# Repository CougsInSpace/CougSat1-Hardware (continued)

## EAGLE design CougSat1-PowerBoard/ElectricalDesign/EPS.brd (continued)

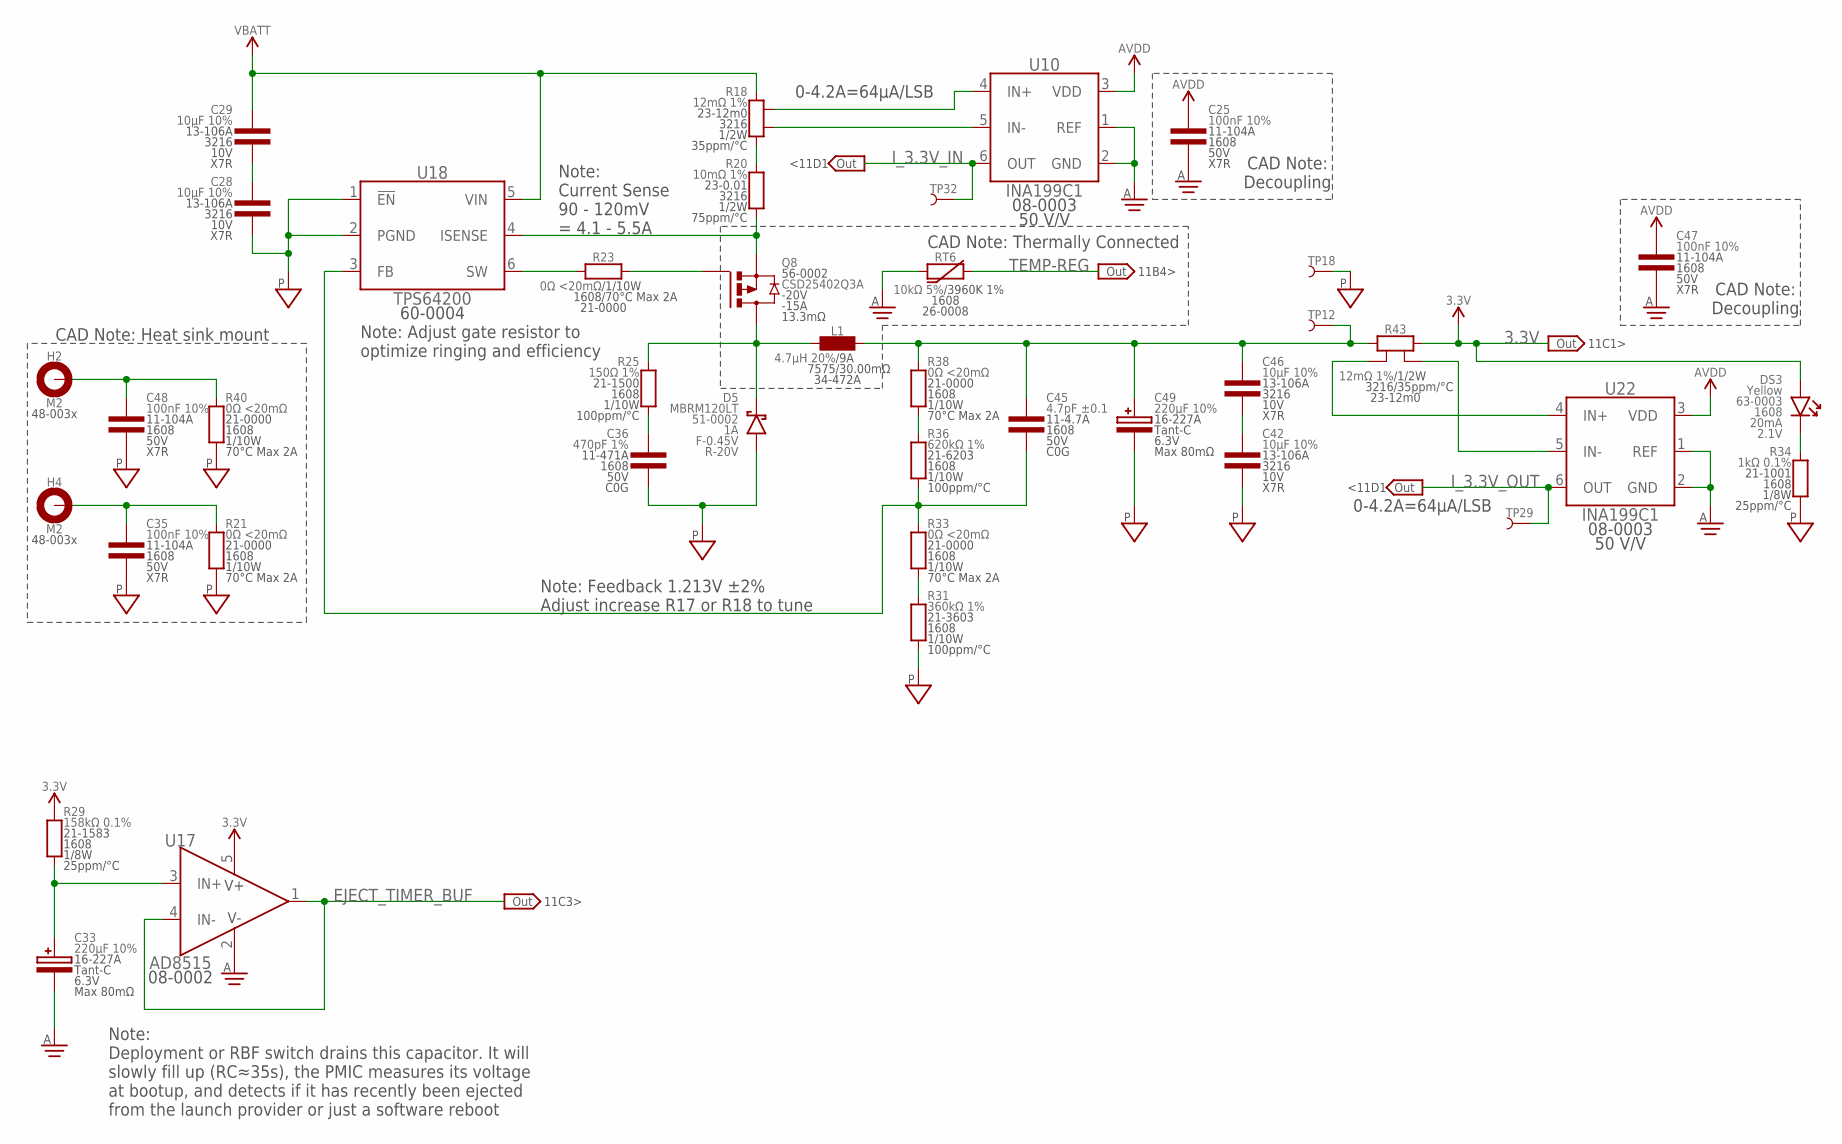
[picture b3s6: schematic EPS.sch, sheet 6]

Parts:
C25, C35, C47, C48: 100nF 10%; 1608
C28, C29, C42, C46: 10µF 10%; 3216
C33, C49: 220µF 10%; 7132-POL
C36: 470pF 1%; 1608
C45: 4.7pF ±0.1; 1608
D5: MBRM120LT; POWERMITE
DS3: Yellow; 1608-POL
H2, H4: M2; MOUNTING_HOLE-2.2
L1: 4.7µH 20%; 7575
Q8: CSD25402Q3A; SON-3333
R18, R43: 12mΩ 1%; 3216-KELVIN
R20: 10mΩ 1%; 3216
R21, R23, R33, R38, R40: 0Ω <20mΩ; 1608
R25: 150Ω 1%; 1608
R29: 158kΩ 0.1%; 1608
R31: 360kΩ 1%; 1608
R34: 1kΩ 0.1%; 1608
R36: 620kΩ 1%; 1608
RT6: 10kΩ 5%; 1608
TP12, TP29, TP32: TEST_POINT-SMD-C-1.25; SMD-C-1.25
TP18: TEST_POINT-THT-0.7; THT-0.7
U10, U22: INA199C1; SOT363
U17: AD8515; SOT23-5
U18: TPS64200; SOT23-6

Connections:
3.3V: DS3.A, R29.2, R43.2, U17.5 (V+); also elsewhere on the board
3.3V_I: C45.1, C46.1, C49.A, L1.2, R38.2, R43.1, TP12.1
3.3V_ISENS: Q8.5 (S), Q8.6 (S), Q8.7 (S), Q8.8 (S), Q8.PAD (S), R20.1, U18.4 (ISENSE)
3.3V_LED: DS3.C, R34.2
3.3V_REG_BUCK_NODE: D5.C, L1.1, Q8.1 (D), Q8.2 (D), Q8.3 (D), R25.2
3.3V_REG_FB: C45.2, R33.2, R36.1, U18.3 (FB)
3.3V_REG_FBRES_HIGH: R36.2, R38.1
3.3V_REG_FBRES_LOW: R31.2, R33.1
3.3V_REG_INCAP: C28.1, C29.2
3.3V_REG_OUTCAP: C42.1, C46.2
3.3V_REG_RSENS: R18.1, R20.2
3.3V_REG_SNUBBER: C36.1, R25.1
3.3V_REG_SW: R23.1, U18.6 (SW)
3.3V_REG_SW_GATE: Q8.4 (G), R23.2
AGND: C25.2, C33.C, C47.2, RT6.1, U10.1 (REF), U10.2 (GND), U17.2 (V-), U22.1 (REF), U22.2 (GND); also elsewhere on the board
AVDD: C25.1, C47.1, U10.3 (VDD), U22.3 (VDD); also elsewhere on the board
CHASSIS_REG1: C48.1, H2.1, H2.V1, H2.V2, H2.V3, H2.V4, H2.V5, H2.V6, H2.V7, H2.V8, R40.2
CHASSIS_REG2: C35.1, H4.1, H4.V1, H4.V2, H4.V3, H4.V4, H4.V5, H4.V6, H4.V7, H4.V8, R21.2
EJECT_TIMER: C33.A, R29.1, U17.3 (IN+)
EJECT_TIMER_BUF: U17.1 (OUT), U17.4 (IN-); also elsewhere on the board
I_3.3V_IN: TP32.1, U10.6 (OUT); also elsewhere on the board
I_3.3V_IN_N: R18.1-KELVIN, U10.5 (IN-)
I_3.3V_IN_P: R18.2-KELVIN, U10.4 (IN+)
I_3.3V_OUT: TP29.1, U22.6 (OUT); also elsewhere on the board
I_3.3V_OUT_N: R43.2-KELVIN, U22.5 (IN-)
I_3.3V_OUT_P: R43.1-KELVIN, U22.4 (IN+)
PGND: C28.2, C35.2, C36.2, C42.2, C48.2, C49.C, D5.A, R21.1, R31.1, R34.1, R40.1, TP18.1, U18.1 (!EN), U18.2 (PGND); also elsewhere on the board
TEMP-REG: RT6.2; also elsewhere on the board
VBATT: C29.1, R18.2, U18.5 (VIN); also elsewhere on the board

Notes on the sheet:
Note: Feedback 1.213V ±2% Adjust increase R17 or R18 to tune
Note: Current Sense 90 - 120mV = 4.1 - 5.5A
CAD Note: Thermally Connected
CAD Note: Heat sink mount
Note: Adjust gate resistor to optimize ringing and efficiency
0-4.2A=64µA/LSB
CAD Note: Decoupling
Note: Deployment or RBF switch drains this capacitor. It will slowly fill up (RC≈35s), the PMIC measures its voltage at bootup, and detects if it has recently been ejected from the launch provider or just a software reboot
<11D1
11C1>
11B4>
11C3>

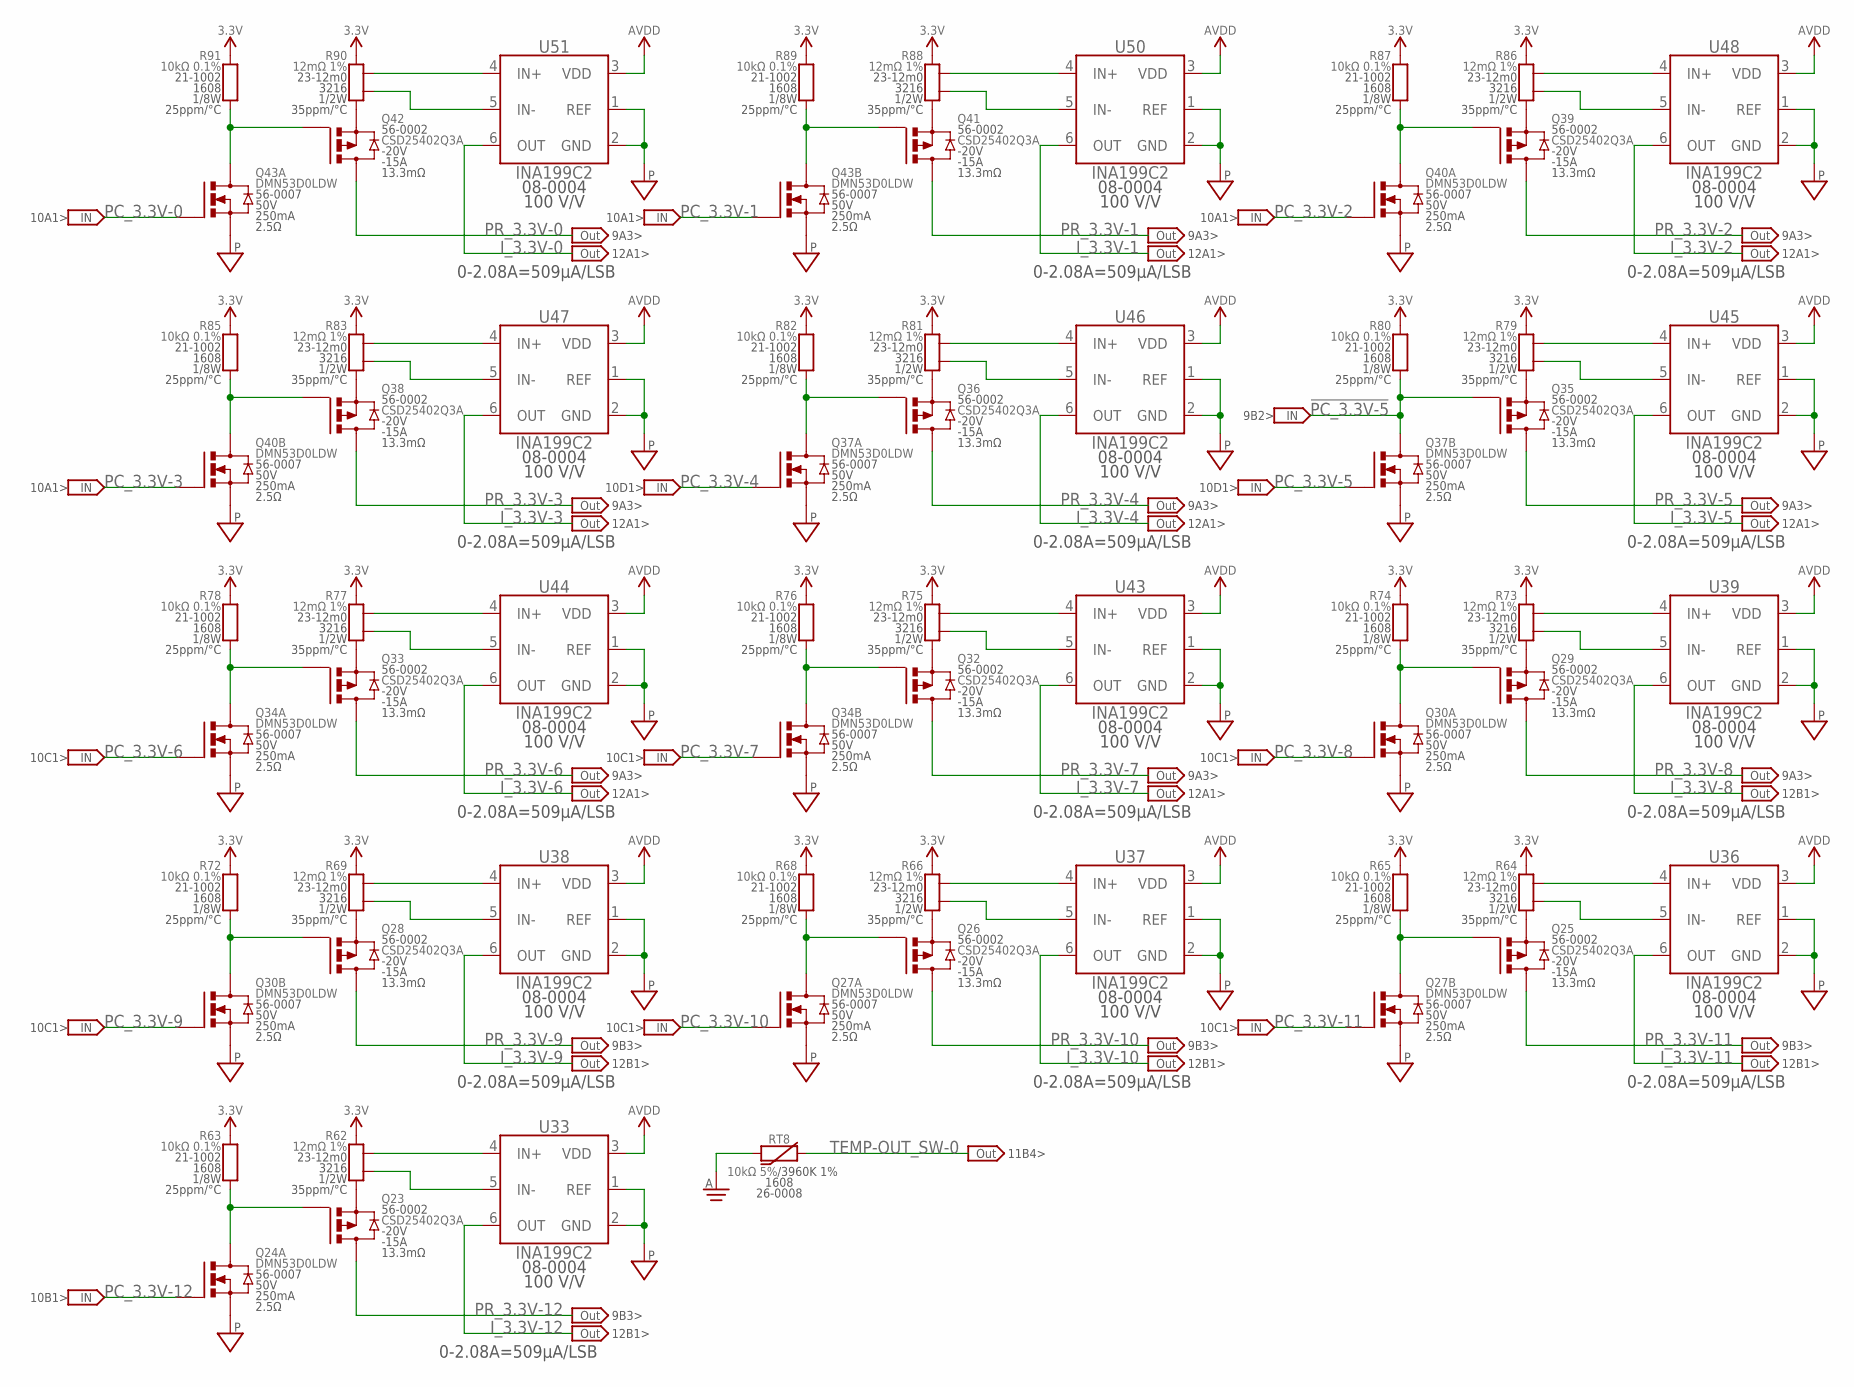
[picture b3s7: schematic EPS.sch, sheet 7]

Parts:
Q23, Q25, Q26, Q28, Q29, Q32, Q33, Q35, Q36, Q38, Q39, Q41, Q42: CSD25402Q3A; SON-3333
Q24, Q27, Q30, Q34, Q37, Q40, Q43: DMN53D0LDW; SOT363
R62, R64, R66, R69, R73, R75, R77, R79, R81, R83, R86, R88, R90: 12mΩ 1%; 3216-KELVIN
R63, R65, R68, R72, R74, R76, R78, R80, R82, R85, R87, R89, R91: 10kΩ 0.1%; 1608
RT8: 10kΩ 5%; 1608
U33, U36, U37, U38, U39, U43, U44, U45, U46, U47, U48, U50, U51: INA199C2; SOT363

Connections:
3.3V: R62.2, R63.2, R64.2, R65.2, R66.2, R68.2, R69.2, R72.2, R73.2, R74.2, R75.2, R76.2, R77.2, R78.2, R79.2, R80.2, R81.2, R82.2, R83.2, R85.2, R86.2, R87.2, R88.2, R89.2, R90.2, R91.2; also elsewhere on the board
!PC_3.3V-0: Q42.4 (G), Q43.6 (D), R91.1
!PC_3.3V-1: Q41.4 (G), Q43.3 (D), R89.1
!PC_3.3V-2: Q39.4 (G), Q40.6 (D), R87.1
!PC_3.3V-3: Q38.4 (G), Q40.3 (D), R85.1
!PC_3.3V-4: Q36.4 (G), Q37.6 (D), R82.1
!PC_3.3V-5: Q35.4 (G), Q37.3 (D), R80.1; also elsewhere on the board
!PC_3.3V-6: Q33.4 (G), Q34.6 (D), R78.1
!PC_3.3V-7: Q32.4 (G), Q34.3 (D), R76.1
!PC_3.3V-8: Q29.4 (G), Q30.6 (D), R74.1
!PC_3.3V-9: Q28.4 (G), Q30.3 (D), R72.1
!PC_3.3V-10: Q26.4 (G), Q27.6 (D), R68.1
!PC_3.3V-11: Q25.4 (G), Q27.3 (D), R65.1
!PC_3.3V-12: Q23.4 (G), Q24.6 (D), R63.1
AGND: RT8.1; also elsewhere on the board
AVDD: U33.3 (VDD), U36.3 (VDD), U37.3 (VDD), U38.3 (VDD), U39.3 (VDD), U43.3 (VDD), U44.3 (VDD), U45.3 (VDD), U46.3 (VDD), U47.3 (VDD), U48.3 (VDD), U50.3 (VDD), U51.3 (VDD); also elsewhere on the board
I_3.3V-0: U51.6 (OUT); also elsewhere on the board
I_3.3V-0_N: R90.1-KELVIN, U51.5 (IN-)
I_3.3V-0_P: R90.2-KELVIN, U51.4 (IN+)
I_3.3V-1: U50.6 (OUT); also elsewhere on the board
I_3.3V-1_N: R88.1-KELVIN, U50.5 (IN-)
I_3.3V-1_P: R88.2-KELVIN, U50.4 (IN+)
I_3.3V-2: U48.6 (OUT); also elsewhere on the board
I_3.3V-2_N: R86.1-KELVIN, U48.5 (IN-)
I_3.3V-2_P: R86.2-KELVIN, U48.4 (IN+)
I_3.3V-3: U47.6 (OUT); also elsewhere on the board
I_3.3V-3_N: R83.1-KELVIN, U47.5 (IN-)
I_3.3V-3_P: R83.2-KELVIN, U47.4 (IN+)
I_3.3V-4: U46.6 (OUT); also elsewhere on the board
I_3.3V-4_N: R81.1-KELVIN, U46.5 (IN-)
I_3.3V-4_P: R81.2-KELVIN, U46.4 (IN+)
I_3.3V-5: U45.6 (OUT); also elsewhere on the board
I_3.3V-5_N: R79.1-KELVIN, U45.5 (IN-)
I_3.3V-5_P: R79.2-KELVIN, U45.4 (IN+)
I_3.3V-6: U44.6 (OUT); also elsewhere on the board
I_3.3V-6_N: R77.1-KELVIN, U44.5 (IN-)
I_3.3V-6_P: R77.2-KELVIN, U44.4 (IN+)
I_3.3V-7: U43.6 (OUT); also elsewhere on the board
I_3.3V-7_N: R75.1-KELVIN, U43.5 (IN-)
I_3.3V-7_P: R75.2-KELVIN, U43.4 (IN+)
I_3.3V-8: U39.6 (OUT); also elsewhere on the board
I_3.3V-8_N: R73.1-KELVIN, U39.5 (IN-)
I_3.3V-8_P: R73.2-KELVIN, U39.4 (IN+)
I_3.3V-9: U38.6 (OUT); also elsewhere on the board
I_3.3V-9_N: R69.1-KELVIN, U38.5 (IN-)
I_3.3V-9_P: R69.2-KELVIN, U38.4 (IN+)
I_3.3V-10: U37.6 (OUT); also elsewhere on the board
I_3.3V-10_N: R66.1-KELVIN, U37.5 (IN-)
I_3.3V-10_P: R66.2-KELVIN, U37.4 (IN+)
I_3.3V-11: U36.6 (OUT); also elsewhere on the board
I_3.3V-11_N: R64.1-KELVIN, U36.5 (IN-)
I_3.3V-11_P: R64.2-KELVIN, U36.4 (IN+)
I_3.3V-12: U33.6 (OUT); also elsewhere on the board
I_3.3V-12_N: R62.1-KELVIN, U33.5 (IN-)
I_3.3V-12_P: R62.2-KELVIN, U33.4 (IN+)
PC_3.3V-0: Q43.2 (G); also elsewhere on the board
PC_3.3V-1: Q43.5 (G); also elsewhere on the board
PC_3.3V-2: Q40.2 (G); also elsewhere on the board
PC_3.3V-3: Q40.5 (G); also elsewhere on the board
PC_3.3V-4: Q37.2 (G); also elsewhere on the board
PC_3.3V-5: Q37.5 (G); also elsewhere on the board
PC_3.3V-6: Q34.2 (G); also elsewhere on the board
PC_3.3V-7: Q34.5 (G); also elsewhere on the board
PC_3.3V-8: Q30.2 (G); also elsewhere on the board
PC_3.3V-9: Q30.5 (G); also elsewhere on the board
PC_3.3V-10: Q27.2 (G); also elsewhere on the board
PC_3.3V-11: Q27.5 (G); also elsewhere on the board
PC_3.3V-12: Q24.2 (G); also elsewhere on the board
PGND: Q24.1 (S), Q27.1 (S), Q27.4 (S), Q30.1 (S), Q30.4 (S), Q34.1 (S), Q34.4 (S), Q37.1 (S), Q37.4 (S), Q40.1 (S), Q40.4 (S), Q43.1 (S), Q43.4 (S), U33.1 (REF), U33.2 (GND), U36.1 (REF), U36.2 (GND), U37.1 (REF), U37.2 (GND), U38.1 (REF), U38.2 (GND), U39.1 (REF), U39.2 (GND), U43.1 (REF), U43.2 (GND), U44.1 (REF), U44.2 (GND), U45.1 (REF), U45.2 (GND), U46.1 (REF), U46.2 (GND), U47.1 (REF), U47.2 (GND), U48.1 (REF), U48.2 (GND), U50.1 (REF), U50.2 (GND), U51.1 (REF), U51.2 (GND); also elsewhere on the board
PR_3.3V-0: Q42.1 (D), Q42.2 (D), Q42.3 (D); also elsewhere on the board
PR_3.3V-1: Q41.1 (D), Q41.2 (D), Q41.3 (D); also elsewhere on the board
PR_3.3V-2: Q39.1 (D), Q39.2 (D), Q39.3 (D); also elsewhere on the board
PR_3.3V-3: Q38.1 (D), Q38.2 (D), Q38.3 (D); also elsewhere on the board
PR_3.3V-4: Q36.1 (D), Q36.2 (D), Q36.3 (D); also elsewhere on the board
PR_3.3V-5: Q35.1 (D), Q35.2 (D), Q35.3 (D); also elsewhere on the board
PR_3.3V-6: Q33.1 (D), Q33.2 (D), Q33.3 (D); also elsewhere on the board
PR_3.3V-7: Q32.1 (D), Q32.2 (D), Q32.3 (D); also elsewhere on the board
PR_3.3V-8: Q29.1 (D), Q29.2 (D), Q29.3 (D); also elsewhere on the board
PR_3.3V-9: Q28.1 (D), Q28.2 (D), Q28.3 (D); also elsewhere on the board
PR_3.3V-10: Q26.1 (D), Q26.2 (D), Q26.3 (D); also elsewhere on the board
PR_3.3V-11: Q25.1 (D), Q25.2 (D), Q25.3 (D); also elsewhere on the board
PR_3.3V-12: Q23.1 (D), Q23.2 (D), Q23.3 (D); also elsewhere on the board
PR_FET_3.3V-0: Q42.5 (S), Q42.6 (S), Q42.7 (S), Q42.8 (S), Q42.PAD (S), R90.1
PR_FET_3.3V-1: Q41.5 (S), Q41.6 (S), Q41.7 (S), Q41.8 (S), Q41.PAD (S), R88.1
PR_FET_3.3V-2: Q39.5 (S), Q39.6 (S), Q39.7 (S), Q39.8 (S), Q39.PAD (S), R86.1
PR_FET_3.3V-3: Q38.5 (S), Q38.6 (S), Q38.7 (S), Q38.8 (S), Q38.PAD (S), R83.1
PR_FET_3.3V-4: Q36.5 (S), Q36.6 (S), Q36.7 (S), Q36.8 (S), Q36.PAD (S), R81.1
PR_FET_3.3V-5: Q35.5 (S), Q35.6 (S), Q35.7 (S), Q35.8 (S), Q35.PAD (S), R79.1
PR_FET_3.3V-6: Q33.5 (S), Q33.6 (S), Q33.7 (S), Q33.8 (S), Q33.PAD (S), R77.1
PR_FET_3.3V-7: Q32.5 (S), Q32.6 (S), Q32.7 (S), Q32.8 (S), Q32.PAD (S), R75.1
PR_FET_3.3V-8: Q29.5 (S), Q29.6 (S), Q29.7 (S), Q29.8 (S), Q29.PAD (S), R73.1
PR_FET_3.3V-9: Q28.5 (S), Q28.6 (S), Q28.7 (S), Q28.8 (S), Q28.PAD (S), R69.1
PR_FET_3.3V-10: Q26.5 (S), Q26.6 (S), Q26.7 (S), Q26.8 (S), Q26.PAD (S), R66.1
PR_FET_3.3V-11: Q25.5 (S), Q25.6 (S), Q25.7 (S), Q25.8 (S), Q25.PAD (S), R64.1
PR_FET_3.3V-12: Q23.5 (S), Q23.6 (S), Q23.7 (S), Q23.8 (S), Q23.PAD (S), R62.1
TEMP-OUT_SW-0: RT8.2; also elsewhere on the board

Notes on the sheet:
0-2.08A=509µA/LSB
9A3>
9B3>
12A1>
12B1>
11B4>
10A1>
10B1>
10C1>
10D1>
9B2>

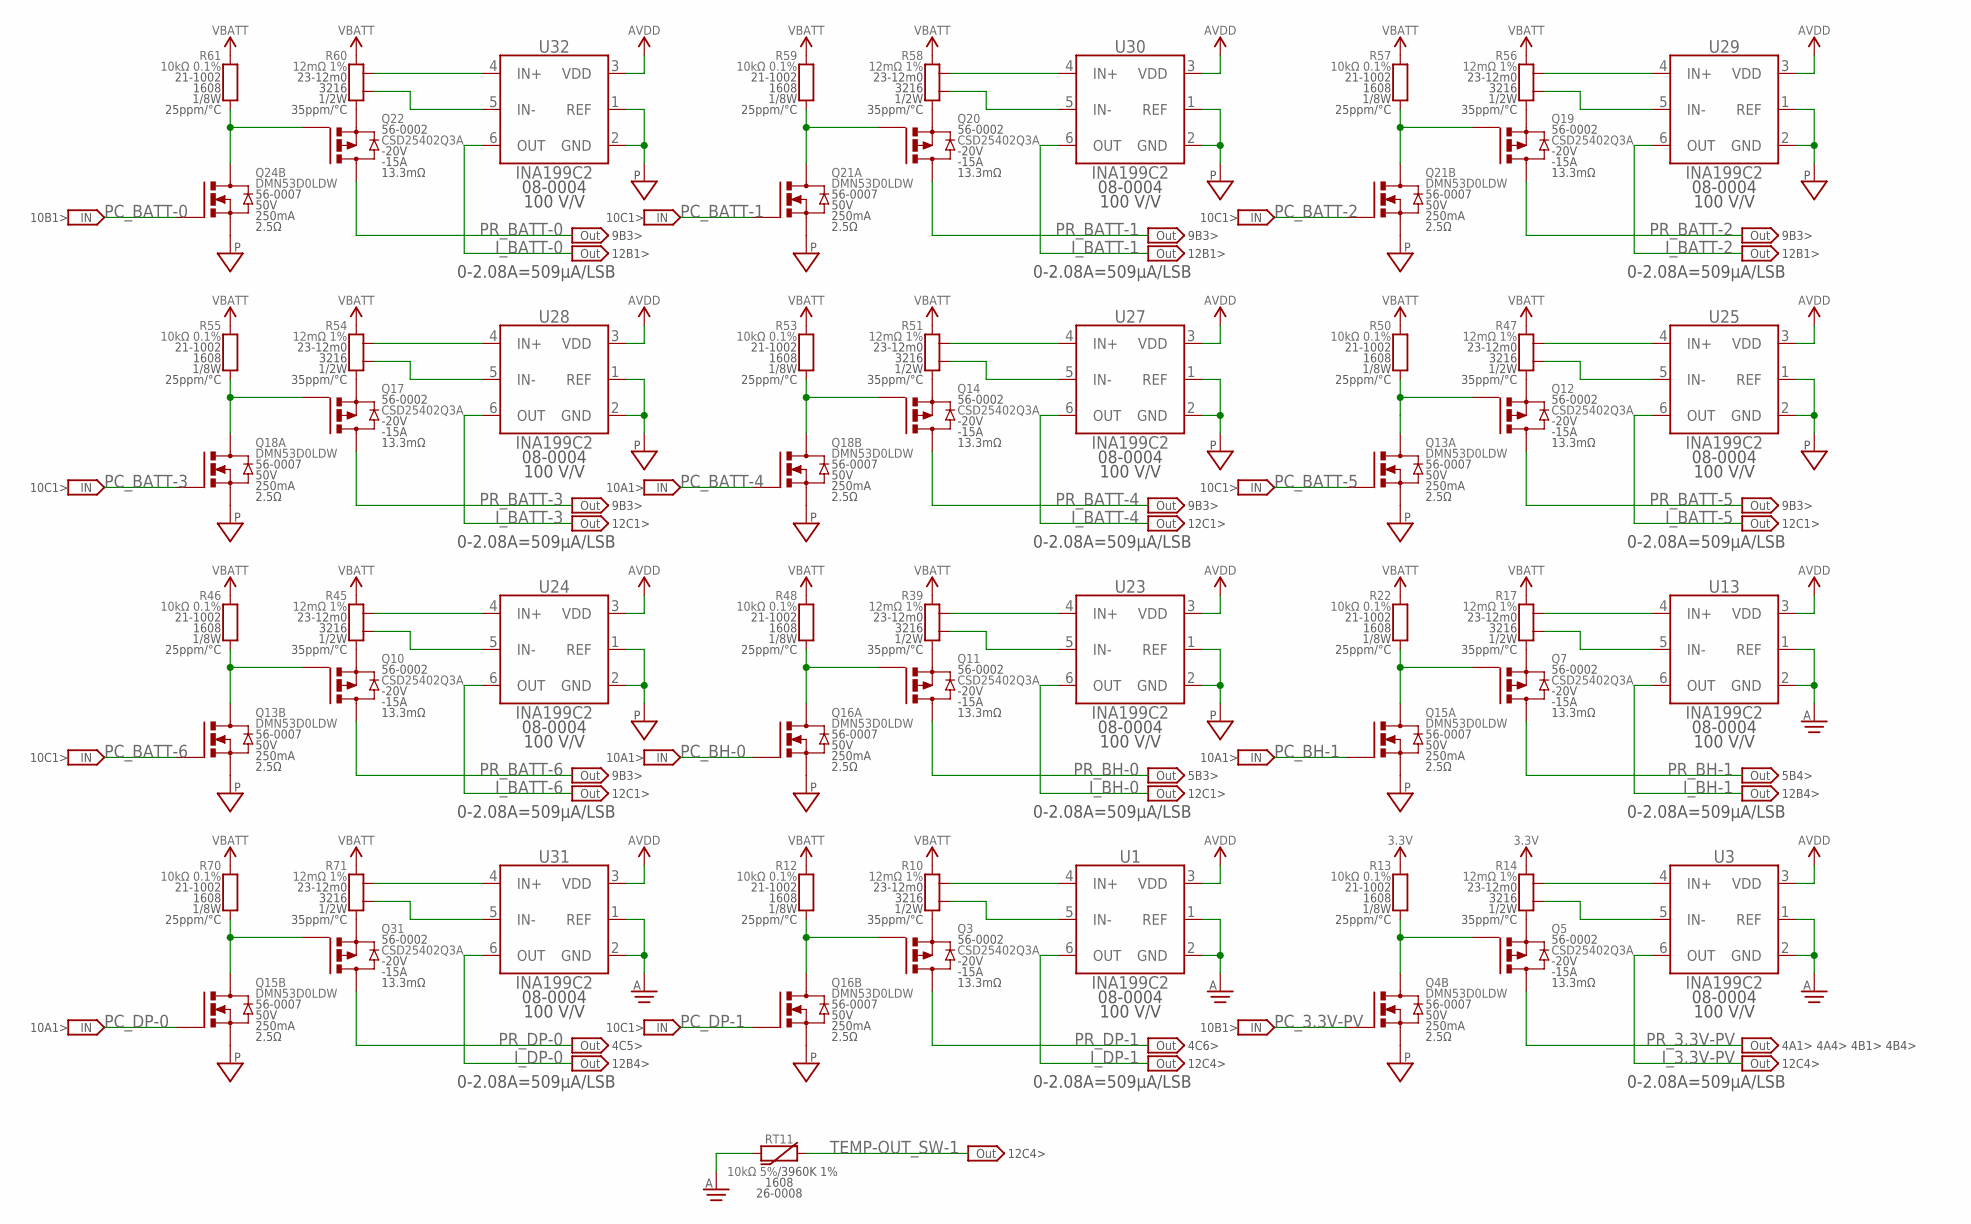
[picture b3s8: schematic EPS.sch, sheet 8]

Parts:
Q3, Q5, Q7, Q10, Q11, Q12, Q14, Q17, Q19, Q20, Q22, Q31: CSD25402Q3A; SON-3333
Q4, Q13, Q15, Q16, Q18, Q21, Q24: DMN53D0LDW; SOT363
R10, R14, R17, R39, R45, R47, R51, R54, R56, R58, R60, R71: 12mΩ 1%; 3216-KELVIN
R12, R13, R22, R46, R48, R50, R53, R55, R57, R59, R61, R70: 10kΩ 0.1%; 1608
RT11: 10kΩ 5%; 1608
U1, U3, U13, U23, U24, U25, U27, U28, U29, U30, U31, U32: INA199C2; SOT363

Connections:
3.3V: R13.2, R14.2; also elsewhere on the board
!PC_3.3V-PV: Q4.3 (D), Q5.4 (G), R13.1
!PC_BATT-0: Q22.4 (G), Q24.3 (D), R61.1
!PC_BATT-1: Q20.4 (G), Q21.6 (D), R59.1
!PC_BATT-2: Q19.4 (G), Q21.3 (D), R57.1
!PC_BATT-3: Q17.4 (G), Q18.6 (D), R55.1
!PC_BATT-4: Q14.4 (G), Q18.3 (D), R53.1
!PC_BATT-5: Q12.4 (G), Q13.6 (D), R50.1
!PC_BATT-6: Q10.4 (G), Q13.3 (D), R46.1
!PC_BH-0: Q11.4 (G), Q16.6 (D), R48.1
!PC_BH-1: Q7.4 (G), Q15.6 (D), R22.1
!PC_DP-0: Q15.3 (D), Q31.4 (G), R70.1
!PC_DP-1: Q3.4 (G), Q16.3 (D), R12.1
AGND: RT11.1, U1.1 (REF), U1.2 (GND), U3.1 (REF), U3.2 (GND), U13.1 (REF), U13.2 (GND), U31.1 (REF), U31.2 (GND); also elsewhere on the board
AVDD: U1.3 (VDD), U3.3 (VDD), U13.3 (VDD), U23.3 (VDD), U24.3 (VDD), U25.3 (VDD), U27.3 (VDD), U28.3 (VDD), U29.3 (VDD), U30.3 (VDD), U31.3 (VDD), U32.3 (VDD); also elsewhere on the board
I_3.3V-PV: U3.6 (OUT); also elsewhere on the board
I_3.3V-PV_N: R14.1-KELVIN, U3.5 (IN-)
I_3.3V-PV_P: R14.2-KELVIN, U3.4 (IN+)
I_BATT-0: U32.6 (OUT); also elsewhere on the board
I_BATT-0_N: R60.1-KELVIN, U32.5 (IN-)
I_BATT-0_P: R60.2-KELVIN, U32.4 (IN+)
I_BATT-1: U30.6 (OUT); also elsewhere on the board
I_BATT-1_N: R58.1-KELVIN, U30.5 (IN-)
I_BATT-1_P: R58.2-KELVIN, U30.4 (IN+)
I_BATT-2: U29.6 (OUT); also elsewhere on the board
I_BATT-2_N: R56.1-KELVIN, U29.5 (IN-)
I_BATT-2_P: R56.2-KELVIN, U29.4 (IN+)
I_BATT-3: U28.6 (OUT); also elsewhere on the board
I_BATT-3_N: R54.1-KELVIN, U28.5 (IN-)
I_BATT-3_P: R54.2-KELVIN, U28.4 (IN+)
I_BATT-4: U27.6 (OUT); also elsewhere on the board
I_BATT-4_N: R51.1-KELVIN, U27.5 (IN-)
I_BATT-4_P: R51.2-KELVIN, U27.4 (IN+)
I_BATT-5: U25.6 (OUT); also elsewhere on the board
I_BATT-5_N: R47.1-KELVIN, U25.5 (IN-)
I_BATT-5_P: R47.2-KELVIN, U25.4 (IN+)
I_BATT-6: U24.6 (OUT); also elsewhere on the board
I_BATT-6_N: R45.1-KELVIN, U24.5 (IN-)
I_BATT-6_P: R45.2-KELVIN, U24.4 (IN+)
I_BH-0: U23.6 (OUT); also elsewhere on the board
I_BH-0_N: R39.1-KELVIN, U23.5 (IN-)
I_BH-0_P: R39.2-KELVIN, U23.4 (IN+)
I_BH-1: U13.6 (OUT); also elsewhere on the board
I_BH-1_N: R17.1-KELVIN, U13.5 (IN-)
I_BH-1_P: R17.2-KELVIN, U13.4 (IN+)
I_DP-0: U31.6 (OUT); also elsewhere on the board
I_DP-0_N: R71.1-KELVIN, U31.5 (IN-)
I_DP-0_P: R71.2-KELVIN, U31.4 (IN+)
I_DP-1: U1.6 (OUT); also elsewhere on the board
I_DP-1_N: R10.1-KELVIN, U1.5 (IN-)
I_DP-1_P: R10.2-KELVIN, U1.4 (IN+)
PC_3.3V-PV: Q4.5 (G); also elsewhere on the board
PC_BATT-0: Q24.5 (G); also elsewhere on the board
PC_BATT-1: Q21.2 (G); also elsewhere on the board
PC_BATT-2: Q21.5 (G); also elsewhere on the board
PC_BATT-3: Q18.2 (G); also elsewhere on the board
PC_BATT-4: Q18.5 (G); also elsewhere on the board
PC_BATT-5: Q13.2 (G); also elsewhere on the board
PC_BATT-6: Q13.5 (G); also elsewhere on the board
PC_BH-0: Q16.2 (G); also elsewhere on the board
PC_BH-1: Q15.2 (G); also elsewhere on the board
PC_DP-0: Q15.5 (G); also elsewhere on the board
PC_DP-1: Q16.5 (G); also elsewhere on the board
PGND: Q4.4 (S), Q13.1 (S), Q13.4 (S), Q15.1 (S), Q15.4 (S), Q16.1 (S), Q16.4 (S), Q18.1 (S), Q18.4 (S), Q21.1 (S), Q21.4 (S), Q24.4 (S), U23.1 (REF), U23.2 (GND), U24.1 (REF), U24.2 (GND), U25.1 (REF), U25.2 (GND), U27.1 (REF), U27.2 (GND), U28.1 (REF), U28.2 (GND), U29.1 (REF), U29.2 (GND), U30.1 (REF), U30.2 (GND), U32.1 (REF), U32.2 (GND); also elsewhere on the board
PR_3.3V-PV: Q5.1 (D), Q5.2 (D), Q5.3 (D); also elsewhere on the board
PR_BATT-0: Q22.1 (D), Q22.2 (D), Q22.3 (D); also elsewhere on the board
PR_BATT-1: Q20.1 (D), Q20.2 (D), Q20.3 (D); also elsewhere on the board
PR_BATT-2: Q19.1 (D), Q19.2 (D), Q19.3 (D); also elsewhere on the board
PR_BATT-3: Q17.1 (D), Q17.2 (D), Q17.3 (D); also elsewhere on the board
PR_BATT-4: Q14.1 (D), Q14.2 (D), Q14.3 (D); also elsewhere on the board
PR_BATT-5: Q12.1 (D), Q12.2 (D), Q12.3 (D); also elsewhere on the board
PR_BATT-6: Q10.1 (D), Q10.2 (D), Q10.3 (D); also elsewhere on the board
PR_BH-0: Q11.1 (D), Q11.2 (D), Q11.3 (D); also elsewhere on the board
PR_BH-1: Q7.1 (D), Q7.2 (D), Q7.3 (D); also elsewhere on the board
PR_DP-0: Q31.1 (D), Q31.2 (D), Q31.3 (D); also elsewhere on the board
PR_DP-1: Q3.1 (D), Q3.2 (D), Q3.3 (D); also elsewhere on the board
PR_FET_3.3V-21: Q31.5 (S), Q31.6 (S), Q31.7 (S), Q31.8 (S), Q31.PAD (S), R71.1
PR_FET_3.3V-22: Q3.5 (S), Q3.6 (S), Q3.7 (S), Q3.8 (S), Q3.PAD (S), R10.1
PR_FET_3.3V-PV: Q5.5 (S), Q5.6 (S), Q5.7 (S), Q5.8 (S), Q5.PAD (S), R14.1
PR_FET_BATT-0: Q22.5 (S), Q22.6 (S), Q22.7 (S), Q22.8 (S), Q22.PAD (S), R60.1
PR_FET_BATT-1: Q20.5 (S), Q20.6 (S), Q20.7 (S), Q20.8 (S), Q20.PAD (S), R58.1
PR_FET_BATT-2: Q19.5 (S), Q19.6 (S), Q19.7 (S), Q19.8 (S), Q19.PAD (S), R56.1
PR_FET_BATT-3: Q17.5 (S), Q17.6 (S), Q17.7 (S), Q17.8 (S), Q17.PAD (S), R54.1
PR_FET_BATT-4: Q14.5 (S), Q14.6 (S), Q14.7 (S), Q14.8 (S), Q14.PAD (S), R51.1
PR_FET_BATT-5: Q12.5 (S), Q12.6 (S), Q12.7 (S), Q12.8 (S), Q12.PAD (S), R47.1
PR_FET_BATT-6: Q10.5 (S), Q10.6 (S), Q10.7 (S), Q10.8 (S), Q10.PAD (S), R45.1
PR_FET_BH-0: Q11.5 (S), Q11.6 (S), Q11.7 (S), Q11.8 (S), Q11.PAD (S), R39.1
PR_FET_BH-1: Q7.5 (S), Q7.6 (S), Q7.7 (S), Q7.8 (S), Q7.PAD (S), R17.1
TEMP-OUT_SW-1: RT11.2; also elsewhere on the board
VBATT: R10.2, R12.2, R17.2, R22.2, R39.2, R45.2, R46.2, R47.2, R48.2, R50.2, R51.2, R53.2, R54.2, R55.2, R56.2, R57.2, R58.2, R59.2, R60.2, R61.2, R70.2, R71.2; also elsewhere on the board

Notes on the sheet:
0-2.08A=509µA/LSB
10A1>
10B1>
10C1>
9B3>
5B3>
5B4>
4C5>
4C6>
4A1> 4A4> 4B1> 4B4>
12B1>
12C1>
12B4>
12C4>

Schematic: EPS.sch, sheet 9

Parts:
C30, C32: 100nF 10%; 1608
C52, C53, C54, C56, C58, C60, C62, C70, C71, C73, C76, C79, C80, C82, C84, C88, C89, C94, C95, C103: 10µF 10%; 1608
J6: CougSat Card; CARD-FULL-OPEN+X
Q9: DMN53D0LDW; SOT363
R9, R92: 0Ω <20mΩ; 1608
R11, R16: 10kΩ 0.1%; 1608
RN15, RN18, RN19: 10kΩ 5%; 3264
U14, U15: TXS0102DQM; X2SON-8

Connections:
3.3V: C30.1, C32.1, U14.1 (VCCA), U14.8 (VCCB), U15.1 (VCCA), U15.8 (VCCB); also elsewhere on the board
!PC_3.3V-5: Q9.3 (D); also elsewhere on the board
BUS_CTRL_SYNC: J6.A42 (CTRL_SYNC), J6.B42 (CTRL_SYNC); also elsewhere on the board
BUS_I2C0_IRQ: J6.A45 (BUS_I2C0_IRQ), J6.B45 (BUS_I2C0_IRQ); also elsewhere on the board
BUS_I2C0_SCL: J6.A44 (BUS_I2C0_SCL), J6.B44 (BUS_I2C0_SCL); also elsewhere on the board
BUS_I2C0_SDA: J6.A43 (BUS_I2C0_SDA), J6.B43 (BUS_I2C0_SDA); also elsewhere on the board
BUS_JTAG_TCK: J6.A46 (BUS_JTAG_TCK), U15.7 (B1)
BUS_JTAG_TDI: J6.A47 (BUS_JTAG_TDI), U15.6 (B2)
BUS_JTAG_TDO: J6.A48 (BUS_JTAG_TDO), U14.7 (B1)
BUS_JTAG_TMS: J6.A49 (BUS_JTAG_TMS), U14.6 (B2)
CHASSIS: J6.CHASSIS@1 (CHASSIS), J6.CHASSIS@2 (CHASSIS), J6.CHASSIS@3 (CHASSIS), J6.CHASSIS@4 (CHASSIS), R9.2, R92.2
DGND: C30.2, C32.2, Q9.4 (S), R16.1, U14.4 (DGND), U15.4 (DGND); also elsewhere on the board
JTAG_EN_PMIC: J6.B47 (BUS_JTAG_EN-1), Q9.5 (G), R16.2, U14.5 (OE), U15.5 (OE)
JTAG_TCK: U15.2 (A1); also elsewhere on the board
JTAG_TDI: U15.3 (A2); also elsewhere on the board
JTAG_TDO: U14.2 (A1); also elsewhere on the board
JTAG_TMS: U14.3 (A2); also elsewhere on the board
PC_3.3V-0: RN19.9 (8); also elsewhere on the board
PC_3.3V-1: RN19.1; also elsewhere on the board
PC_3.3V-2: RN19.8 (7); also elsewhere on the board
PC_3.3V-3: RN19.2; also elsewhere on the board
PC_3.3V-4: RN19.7 (6); also elsewhere on the board
PC_3.3V-5: RN19.3; also elsewhere on the board
PC_3.3V-6: RN19.6 (5); also elsewhere on the board
PC_3.3V-7: RN19.4; also elsewhere on the board
PC_3.3V-8: RN18.9 (8); also elsewhere on the board
PC_3.3V-9: RN18.1; also elsewhere on the board
PC_3.3V-10: RN18.8 (7); also elsewhere on the board
PC_3.3V-11: RN18.2; also elsewhere on the board
PC_3.3V-12: RN18.7 (6); also elsewhere on the board
PC_3.3V-PV: R11.1; also elsewhere on the board
PC_BATT-0: RN18.3; also elsewhere on the board
PC_BATT-1: RN18.6 (5); also elsewhere on the board
PC_BATT-2: RN18.4; also elsewhere on the board
PC_BATT-3: RN15.9 (8); also elsewhere on the board
PC_BATT-4: RN15.1; also elsewhere on the board
PC_BATT-5: RN15.8 (7); also elsewhere on the board
PC_BATT-6: RN15.2; also elsewhere on the board
PC_BH-0: RN15.7 (6); also elsewhere on the board
PC_BH-1: RN15.6 (5); also elsewhere on the board
PC_DP-0: RN15.4; also elsewhere on the board
PC_DP-1: RN15.3; also elsewhere on the board
PGND: C52.2, C53.2, C54.2, C56.2, C58.2, C60.2, C62.2, C70.2, C71.2, C73.2, C76.1, C79.1, C80.1, C82.1, C84.1, C88.1, C89.1, C94.1, C95.1, C103.1, J6.A21 (PGND), J6.A22 (PGND), J6.A23 (PGND), J6.B21 (PGND), J6.B22 (PGND), J6.B23 (PGND), J6.B24 (PGND), J6.B25 (PGND), J6.B26 (PGND), J6.B27 (PGND), J6.B28 (PGND), J6.B29 (PGND), R9.1, R11.2, R92.1, RN15.5 (C), RN15.10 (C), RN18.5 (C), RN18.10 (C), RN19.5 (C), RN19.10 (C); also elsewhere on the board
PR_3.3V-0: C103.2, J6.A1 (PR_3.3V-0), J6.B1 (PR_3.3V-0); also elsewhere on the board
PR_3.3V-1: C95.2, J6.A2 (PR_3.3V-1), J6.B2 (PR_3.3V-1); also elsewhere on the board
PR_3.3V-2: C94.2, J6.A3 (PR_3.3V-2), J6.B3 (PR_3.3V-2); also elsewhere on the board
PR_3.3V-3: C89.2, J6.A4 (PR_3.3V-3), J6.B4 (PR_3.3V-3); also elsewhere on the board
PR_3.3V-4: C88.2, J6.A5 (PR_3.3V-4), J6.B5 (PR_3.3V-4); also elsewhere on the board
PR_3.3V-5: C84.2, J6.A6 (PR_3.3V-5), J6.B6 (PR_3.3V-5); also elsewhere on the board
PR_3.3V-6: C82.2, J6.A7 (PR_3.3V-6), J6.B7 (PR_3.3V-6); also elsewhere on the board
PR_3.3V-7: C80.2, J6.A8 (PR_3.3V-7), J6.B8 (PR_3.3V-7); also elsewhere on the board
PR_3.3V-8: C79.2, J6.A9 (PR_3.3V-8), J6.B9 (PR_3.3V-8); also elsewhere on the board
PR_3.3V-9: C76.2, J6.A10 (PR_3.3V-9), J6.B10 (PR_3.3V-9); also elsewhere on the board
PR_3.3V-10: C73.1, J6.A11 (PR_3.3V-10), J6.B11 (PR_3.3V-10); also elsewhere on the board
PR_3.3V-11: C71.1, J6.A12 (PR_3.3V-11), J6.B12 (PR_3.3V-11); also elsewhere on the board
PR_3.3V-12: C70.1, J6.A13 (PR_3.3V-12), J6.B13 (PR_3.3V-12); also elsewhere on the board
PR_BATT-0: C62.1, J6.A14 (PR_BATT-0), J6.B14 (PR_BATT-0); also elsewhere on the board
PR_BATT-1: C60.1, J6.A15 (PR_BATT-1), J6.B15 (PR_BATT-1); also elsewhere on the board
PR_BATT-2: C58.1, J6.A16 (PR_BATT-2), J6.B16 (PR_BATT-2); also elsewhere on the board
PR_BATT-3: C56.1, J6.A17 (PR_BATT-3), J6.B17 (PR_BATT-3); also elsewhere on the board
PR_BATT-4: C54.1, J6.A18 (PR_BATT-4), J6.B18 (PR_BATT-4); also elsewhere on the board
PR_BATT-5: C53.1, J6.A19 (PR_BATT-5), J6.B19 (PR_BATT-5); also elsewhere on the board
PR_BATT-6: C52.1, J6.A20 (PR_BATT-6), J6.B20 (PR_BATT-6); also elsewhere on the board

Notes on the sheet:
CAD Note: Decoupling
Note: STM32 includes JTAG termination
IFJR drives JTAG_EN_PMIC high when programming. This ORing FETs ensure its power rail stays on when programming.
<10A1
10B1>
10C1>
10D1>
10A1>
<10B4>
<10A4>
<10A4
<7B5
7A2>
7A4>
7A6>
7B2>
7B4>
7B6>
7C2>
7C4>
7C6>
7D2>
7D4>
7D6>
8A2>
8A4>
8A6>
8B2>
8B4>
8B6>
8C2>

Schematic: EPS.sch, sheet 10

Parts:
C12, C38, C41, C77, C78, C85, C91: 100nF 10%; 1608
C63, C64: 8pF ±0.25; 1608
C66: 10nF 10%; 1608
C67, C68: 15pF 1%; 1608
DS1: Blue; 1608-POL
J13: SWD; SMD2.54-1X06-R
R15, R84: 1kΩ 0.1%; 1608
R67: 0Ω <20mΩ; 1608
RN1, RN2, RN5: 10kΩ 1%; 1632
TP2, TP3, TP7, TP8, TP14, TP15, TP16, TP17, TP19, TP21, TP24, TP26: TEST_POINT-SMD-C-1.25; SMD-C-1.25
U5, U19, U20: TXS0102DQM; X2SON-8
U41: STM32L476RGT; QFP-64-1010
Y1: 32.768kHz ±10ppm; SMD-3215
Y2: 8MHz ±10ppm; SMD-5032

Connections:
3.3V: C12.1, C38.1, C41.1, C77.1, C78.1, C85.1, C91.1, R15.2, RN1.5 (2), RN1.6 (2), RN1.7 (2), RN1.8 (2), RN2.5 (2), RN2.6 (2), RN2.7 (2), RN2.8 (2), RN5.5 (2), RN5.6 (2), RN5.7 (2), RN5.8 (2), U5.1 (VCCA), U5.8 (VCCB), U19.1 (VCCA), U19.8 (VCCB), U20.1 (VCCA), U20.8 (VCCB), U41.1 (VBAT), U41.19 (VDD), U41.32 (VDD), U41.48 (VDDUSB), U41.64 (VDD); also elsewhere on the board
!NRST: C66.1, J13.5 (!RST), U41.7 (!NRST)
ADC_SEL-0: U41.61 (PB8); also elsewhere on the board
ADC_SEL-1: U41.51 (PC10); also elsewhere on the board
ADC_SEL-2: U41.57 (PB5); also elsewhere on the board
AVDD: U41.13 (VDDA/VREF+); also elsewhere on the board
BOOT0: R67.2, U41.60 (BOOT0)
BUS_CTRL_SYNC: RN1.1, TP19.1, U20.3 (A2); also elsewhere on the board
BUS_I2C0_IRQ: RN1.4 (1), TP26.1, U19.2 (A1); also elsewhere on the board
BUS_I2C0_SCL: RN1.3 (1), TP24.1, U19.3 (A2); also elsewhere on the board
BUS_I2C0_SDA: RN1.2 (1), TP21.1, U20.2 (A1); also elsewhere on the board
BUS_I2C_IRQ: RN2.1, TP17.1, U19.7 (B1), U41.28 (PB2)
BUS_I2C_SCL: RN2.2 (1), TP15.1, U19.6 (B2), U41.29 (PB10)
BUS_I2C_SDA: RN2.3 (1), TP14.1, U20.7 (B1), U41.30 (PB11)
CTRL_SYNC: RN2.4 (1), TP16.1, U20.6 (B2), U41.20 (PA4)
DGND: C12.2, C38.2, C41.2, C63.2, C64.2, C66.2, C67.2, C68.2, C77.2, C78.2, C85.2, C91.2, J13.3 (DGND), R67.1, R84.1, U5.4 (DGND), U19.4 (DGND), U20.4 (DGND), U41.12 (VSSA/VREF-), U41.18 (VSS), U41.31 (VSS), U41.47 (VSS), U41.63 (VSS), Y2.2 (GND), Y2.4 (GND); also elsewhere on the board
I2C_SCL: RN5.4 (1), TP7.1, U5.7 (B1), U41.58 (PB6); also elsewhere on the board
I2C_SDA: RN5.1, TP8.1, U5.6 (B2), U41.59 (PB7); also elsewhere on the board
JTAG_TCK: J13.2 (SWCLK), U41.49 (PA14); also elsewhere on the board
JTAG_TDI: U41.50 (PA15); also elsewhere on the board
JTAG_TDO: J13.6 (SWO), U41.55 (PB3); also elsewhere on the board
JTAG_TMS: J13.4 (SWDIO), U41.46 (PA13); also elsewhere on the board
OSC32_IN: C67.1, U41.3 (PC14), Y1.2
OSC32_OUT: C68.1, U41.4 (PC15), Y1.1
OSC_IN: C63.1, U41.5 (PH0-OSC_IN), Y2.1
OSC_OUT: C64.1, U41.6 (PH1-OSC_OUT), Y2.3 (2)
PC_3.3V-0: U41.43 (PA10); also elsewhere on the board
PC_3.3V-1: U41.44 (PA11); also elsewhere on the board
PC_3.3V-2: U41.41 (PA8); also elsewhere on the board
PC_3.3V-3: U41.42 (PA9); also elsewhere on the board
PC_3.3V-4: U41.39 (PC8); also elsewhere on the board
PC_3.3V-5: U41.40 (PC9); also elsewhere on the board
PC_3.3V-6: U41.37 (PC6); also elsewhere on the board
PC_3.3V-7: U41.38 (PC7); also elsewhere on the board
PC_3.3V-8: U41.35 (PB14); also elsewhere on the board
PC_3.3V-9: U41.36 (PB15); also elsewhere on the board
PC_3.3V-10: U41.33 (PB12); also elsewhere on the board
PC_3.3V-11: U41.34 (PB13); also elsewhere on the board
PC_3.3V-12: U41.26 (PB0); also elsewhere on the board
PC_3.3V-PV: U41.56 (PB4); also elsewhere on the board
PC_BATT-0: U41.27 (PB1); also elsewhere on the board
PC_BATT-1: U41.24 (PC4); also elsewhere on the board
PC_BATT-2: U41.25 (PC5); also elsewhere on the board
PC_BATT-3: U41.8 (PC0); also elsewhere on the board
PC_BATT-4: U41.17 (PA3); also elsewhere on the board
PC_BATT-5: U41.10 (PC2); also elsewhere on the board
PC_BATT-6: U41.9 (PC1); also elsewhere on the board
PC_BH-0: U41.16 (PA2); also elsewhere on the board
PC_BH-1: U41.14 (PA0); also elsewhere on the board
PC_DP-0: U41.15 (PA1); also elsewhere on the board
PC_DP-1: U41.11 (PC3); also elsewhere on the board
PMIC_LED-A: DS1.A, U41.54 (EXTRA_PIN)
PMIC_LED-C: DS1.C, R84.2
PR_3.3V-0: U19.5 (OE), U20.5 (OE); also elsewhere on the board
PR_3.3V-PV: U5.5 (OE); also elsewhere on the board
PV_I2C_SCL: RN5.3 (1), TP3.1, U5.2 (A1); also elsewhere on the board
PV_I2C_SDA: RN5.2 (1), TP2.1, U5.3 (A2); also elsewhere on the board
SPI_MISO: U41.22 (PA6); also elsewhere on the board
SPI_MOSI: U41.23 (PA7); also elsewhere on the board
SPI_SCK: U41.21 (PA5); also elsewhere on the board
SWD_VSENSE: J13.1 (VSENSE), R15.1

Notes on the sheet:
CAD Note: Decoupling
Note: Internal 40kΩ PU
<9C2>
9C2>
<9D2>
<4A1> <4A4> <4B1> <4B4>
<4A1 <4A4 <4B1 <4B4
<10B1>
10B1>
<10A1>
<10A1
<10B1
<10D6
10A1>
10C5>
8C5> 9C6>
8C3> 9C6>
8D3> 9C6>
8D1> 9C6>
8D5> 9D5> 10C6>
8B5> 9C6>
8B3> 9C6>
8B1> 9C6>
8C1> 9C6>
8A1> 9C5>
8A3> 9C5>
8A5> 9C5>
7C5> 9C5>
7D5> 9C5>
7D3> 9C5>
7D1> 9C5>
7A1> 9C3>
7A3> 9C3>
7A5> 9C3>
7B5> 9C3>
7B3> 9C3>
7B1> 9C3>
7C1> 9C3>
7C3> 9C3>
11C3>
